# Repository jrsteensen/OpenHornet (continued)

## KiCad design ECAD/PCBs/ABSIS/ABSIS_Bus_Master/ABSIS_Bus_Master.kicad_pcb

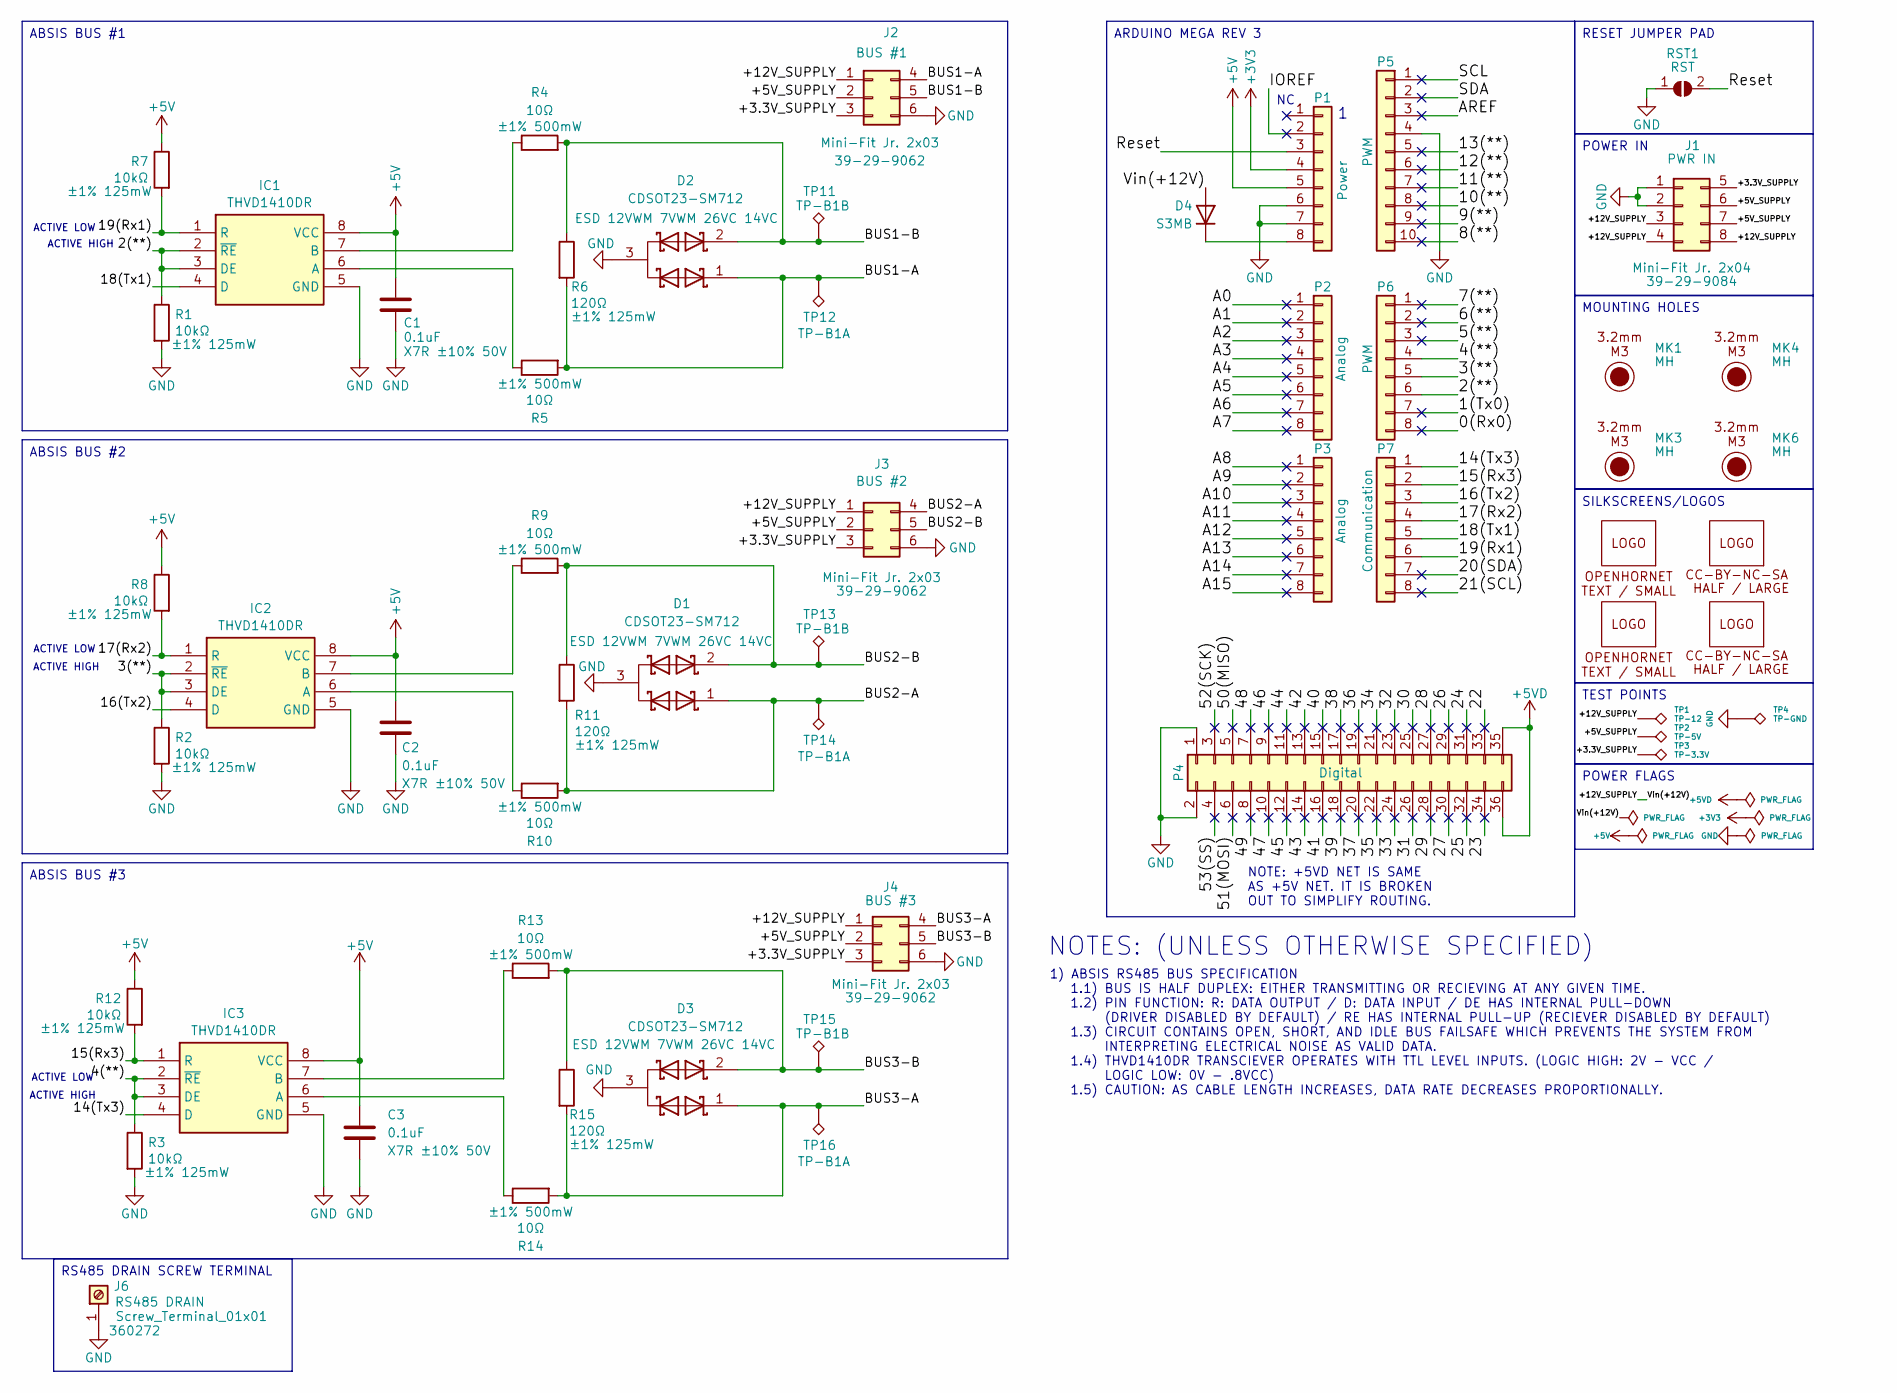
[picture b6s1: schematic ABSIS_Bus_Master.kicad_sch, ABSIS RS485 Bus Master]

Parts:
C1, C2, C3: 0.1uF; C_0805_2012Metric; Manufacturer PN CC0805KRX7R9BB104; LCSC C49678
D1, D2, D3: CDSOT23-SM712; Manufacturer PN CDSOT23-SM712; LCSC C404012
D4: S3MB; D_SMB; Manufacturer PN S3MB; LCSC C47524
IC1, IC2, IC3: THVD1410DR; Manufacturer PN THVD1410DR; LCSC C2671345
J1: Mini-Fit Jr. 2x04; Molex_Mini-Fit_Jr_5566-08A2_2x04_P4.20mm_Vertical; Manufacturer PN 39-29-9084; LCSC C587470
J2, J3, J4: Mini-Fit Jr. 2x03; Molex_Mini-Fit_Jr_5566-06A2_2x03_P4.20mm_Vertical; Manufacturer PN 39-29-9062; LCSC C505177
J6: Screw_Terminal_01x01; TerminalBlock_MetzConnect_360272_1x01_Horizontal_ScrewM2.6; Manufacturer PN 360272
LOGO1, LOGO4: LOGO; LOGO_CC-BY-NC-SA_Half_Large
LOGO2, LOGO3: LOGO; LOGO_OH_Text_Small
MK1, MK3, MK4, MK6: MH; MountingHole_3.2mm_M3_DIN965
P1: Power; PinHeader_1x08_P2.54mm_Vertical
P2, P3: Analog; PinHeader_1x08_P2.54mm_Vertical
P4: Digital; PinHeader_2x18_P2.54mm_Vertical
P5: PWM; PinHeader_1x10_P2.54mm_Vertical
P6: PWM; PinHeader_1x08_P2.54mm_Vertical
P7: Communication; PinHeader_1x08_P2.54mm_Vertical
R1, R2, R3, R7, R8, R12: 10kΩ; R_0805_2012Metric; Manufacturer PN AC0805FR-0710KL; LCSC C140868
R4, R5, R9, R10, R13, R14: 10Ω; R_0805_2012Metric; Manufacturer PN CRCW080510R0FKEAHP; LCSC C844598
R6, R11, R15: 120Ω; R_0805_2012Metric; Manufacturer PN CRCW0805120RFKEA; LCSC C844816
RST1: RST; SolderJumper-2_P1.3mm_Open_RoundedPad1.0x1.5mm
TP1: TP-12; TestPoint_THTPad_D1.5mm_Drill0.7mm
TP2: TP-5V; TestPoint_THTPad_D1.5mm_Drill0.7mm
TP3: TP-3.3V; TestPoint_THTPad_D1.5mm_Drill0.7mm
TP4: TP-GND; TestPoint_THTPad_D1.5mm_Drill0.7mm
TP11, TP13, TP15: TP-B1B; TestPoint_THTPad_D1.5mm_Drill0.7mm
TP12, TP14, TP16: TP-B1A; TestPoint_THTPad_D1.5mm_Drill0.7mm

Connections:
+3V3: P1.4
+5V: C1.2, C2.2, C3.2, IC1.8 (VCC), IC2.8 (VCC), IC3.8 (VCC), P1.5, R7.1, R8.1, R12.1
+5VD: P4.35, P4.36
/0(Rx0): P6.8
/1(Tx0): P6.7
/2(**): IC1.2 (~RE), IC1.3 (DE), P6.6, R1.1
/3(**): IC2.2 (~RE), IC2.3 (DE), P6.5, R2.1
/4(**): IC3.2 (~RE), IC3.3 (DE), P6.4, R3.1
/5(**): P6.3
/6(**): P6.2
/7(**): P6.1
/8(**): P5.10
/9(**): P5.9
/10(**): P5.8
/11(**): P5.7
/12(**): P5.6
/13(**): P5.5
/14(Tx3): IC3.4 (D), P7.1
/15(Rx3): IC3.1 (R), P7.2, R12.2
/16(Tx2): IC2.4 (D), P7.3
/17(Rx2): IC2.1 (R), P7.4, R8.2
/18(Tx1): IC1.4 (D), P7.5
/19(Rx1): IC1.1 (R), P7.6, R7.2
/20(SDA): P7.7
/21(SCL): P7.8
/22: P4.33
/23: P4.34
/24: P4.31
/25: P4.32
/26: P4.29
/27: P4.30
/28: P4.27
/29: P4.28
/30: P4.25
/31: P4.26
/32: P4.23
/33: P4.24
/34: P4.21
/35: P4.22
/36: P4.19
/37: P4.20
/38: P4.17
/39: P4.18
/40: P4.15
/41: P4.16
/42: P4.13
/43: P4.14
/44: P4.11
/45: P4.12
/46: P4.9
/47: P4.10
/48: P4.7
/49: P4.8
/50(MISO): P4.5
/51(MOSI): P4.6
/52(SCK): P4.3
/53(SS): P4.4
/+3.3V_SUPPLY: J1.5, J2.3, J3.3, J4.3, TP3.1 (1_1)
/+5V_SUPPLY: J1.6, J1.7, J2.2, J3.2, J4.2, TP2.1 (1_1)
/+12V_SUPPLY: D4.2 (A), J1.3, J1.4, J1.8, J2.1, J3.1, J4.1, TP1.1 (1_1)
/A0: P2.1
/A1: P2.2
/A2: P2.3
/A3: P2.4
/A4: P2.5
/A5: P2.6
/A6: P2.7
/A7: P2.8
/A8: P3.1
/A9: P3.2
/A10: P3.3
/A11: P3.4
/A12: P3.5
/A13: P3.6
/A14: P3.7
/A15: P3.8
/AREF: P5.3
/BUS1-A: D2.1, J2.4, R5.2, R6.2, TP12.1 (1_1)
/BUS1-B: D2.2, J2.5, R4.2, R6.1, TP11.1 (1_1)
/BUS2-A: D1.1, J3.4, R10.2, R11.2, TP14.1 (1_1)
/BUS2-B: D1.2, J3.5, R9.2, R11.1, TP13.1 (1_1)
/BUS3-A: D3.1, J4.4, R14.2, R15.2, TP16.1 (1_1)
/BUS3-B: D3.2, J4.5, R13.2, R15.1, TP15.1 (1_1)
/IOREF: P1.2
/Reset: P1.3, RST1.2 (B)
/SCL: P5.1
/SDA: P5.2
GND: C1.1, C2.1, C3.1, D1.3, D2.3, D3.3, IC1.5 (GND), IC2.5 (GND), IC3.5 (GND), J1.1, J1.2, J2.6, J3.6, J4.6, J6.1 (Pin_1_1), P1.6, P1.7, P4.1, P4.2, P5.4, R1.2, R2.2, R3.2, RST1.1 (A), TP4.1 (1_1)
unnamed: D4.1 (K), P1.8
unnamed: IC1.6 (A), R5.1
unnamed: IC1.7 (B), R4.1
unnamed: IC2.6 (A), R10.1
unnamed: IC2.7 (B), R9.1
unnamed: IC3.6 (A), R14.1
unnamed: IC3.7 (B), R13.1

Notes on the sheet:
ACTIVE HIGH
ACTIVE LOW
NOTES: (UNLESS OTHERWISE SPECIFIED)
NOTE: +5VD NET IS SAME AS +5V NET. IT IS BROKEN OUT TO SIMPLIFY ROUTING.
1) ABSIS RS485 BUS SPECIFICATION 1.1) BUS IS HALF DUPLEX: EITHER TRANSMITTING OR RECIEVING AT ANY GIVEN TIME. 1.2) PIN FUNCTION: R: DATA OUTPUT / D: DATA INPUT / DE HAS INTERNAL PULL-DOWN (DRIVER DISABLED BY DEFAULT) / RE HAS INTERNAL PULL-UP (RECIEVER DISABLED BY DEFAULT) 1.3) CIRCUIT CONTAINS OPE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
POWER IN
MOUNTING HOLES
POWER FLAGS
ABSIS BUS #1
ABSIS BUS #3
ABSIS BUS #2
RS485 DRAIN SCREW TERMINAL
ARDUINO MEGA REV 3
RESET JUMPER PAD
TEST POINTS
SILKSCREENS/LOGOS

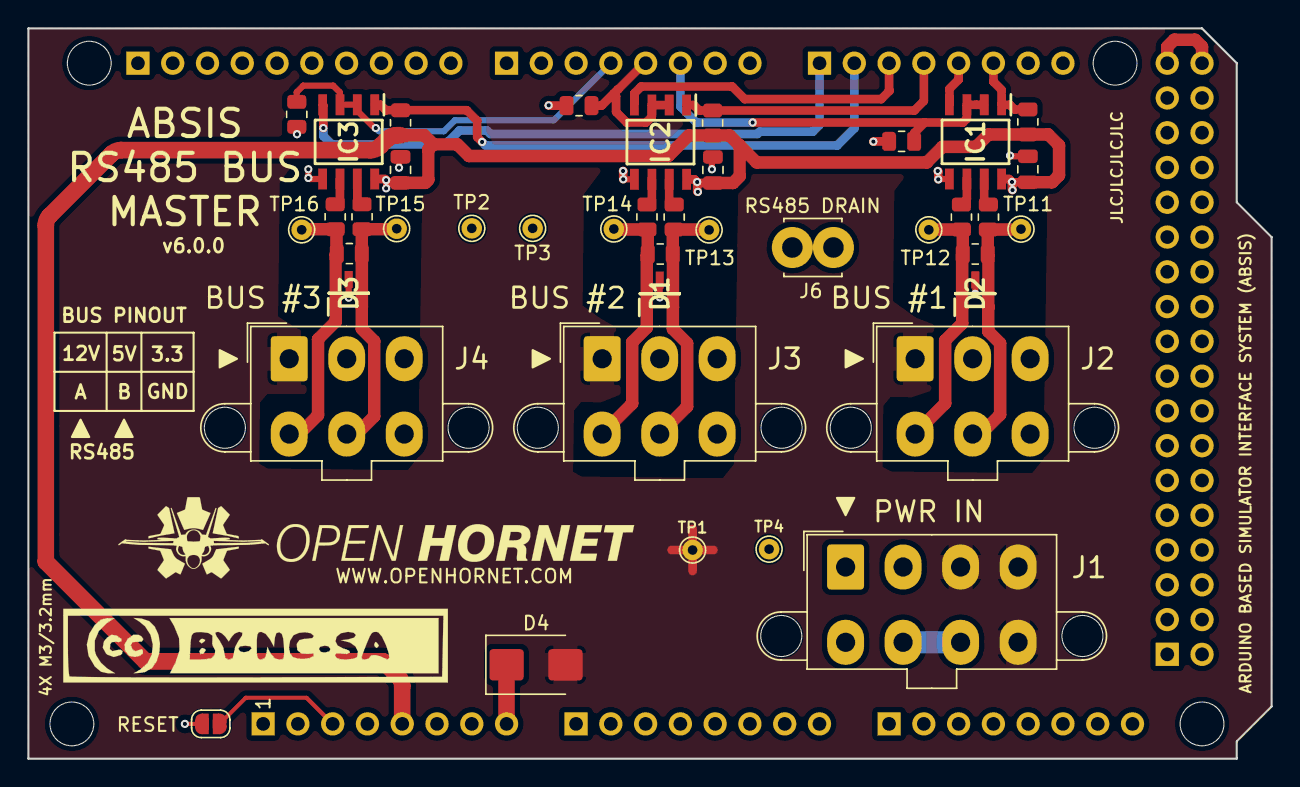
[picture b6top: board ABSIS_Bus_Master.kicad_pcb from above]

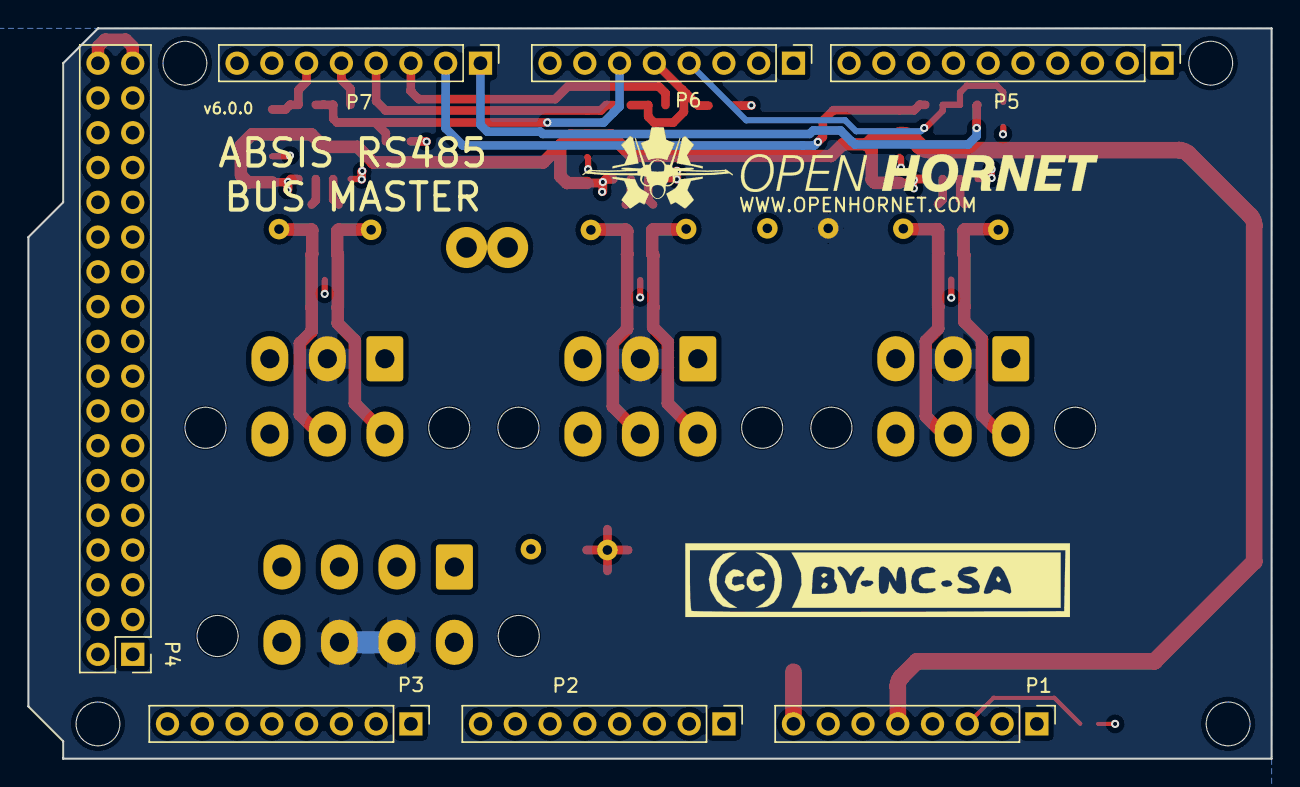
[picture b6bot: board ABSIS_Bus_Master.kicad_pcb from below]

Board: 4 copper layers, 90.8 x 53.3 mm, 56 parts (9 on the bottom side), 29 nets.

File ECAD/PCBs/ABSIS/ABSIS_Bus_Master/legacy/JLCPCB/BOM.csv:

"Reference","Value","Datasheet","Footprint","Qty","DNP","#","LCSC","Manufacturer PN","Description"
"C1,C2,C3","0.1uF","https://datasheet.lcsc.com/szlcsc/YAGEO-CChttps://datasheet.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","Capacitor_SMD:C_0805_2012Metric","3","","1","C49678","CC0805KRX7R9BB104","X7R ±10% 50V"
"D1,D2,D3","CDSOT23-SM712","https://www.lcsc.com/datasheet/C404012.pdf?spm=wm.sxq.inf.gg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","CDSOT23-SM712:CDSOT23-SM712","3","","2","C404012","CDSOT23-SM712","ESD 12VWM 7VWM 26VC 14VC"
"D4","SS54","https://datasheet.lcsc.com/szlcsc/1903042030_MDD-Jiangsu-Yut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","SS54:SS54","1","","3","C22452","SS54","SURFACE MOUNT SCHOTTKY BARRIER RECTIFIER."
"IC1,IC2,IC3","THVD1410DR","https://www.ti.com/lit/ds/symlink/thvd1410.pdf?HQS=dis-dk-nu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","THVD1410DR:THVD1410DR","3","","4","C2671345","THVD1410DR","3.3-V to 5-V RS-485 transceiver with +/-18-kV IEC ESD protection"
"J1","Mini-Fit Jr. 2x04","https://datasheet.lcsc.com/lcsc/2007161933_MOLEX-39299084_C5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","OH_Footprints:Molex_Mini-Fit_Jr_5566-08A2_2x04_P4.20mm_Vertical","1","","5","C587470","39-29-9084",""
"J2,J3,J4","Mini-Fit Jr. 2x03","https://datasheet.lcsc.com/lcsc/2005291105_MOLEX-39299062_C5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","OH_Footprints:Molex_Mini-Fit_Jr_5566-06A2_2x03_P4.20mm_Vertical","3","","6","C505177","39-29-9062",""
"J5","PinHeader_2x11","https://app.adam-tech.com/products/download/data_sheet/20206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","Connector_PinHeader_2.54mm:PinHeader_2x11_P2.54mm_Vertical","1","","7","","PH2-11-UA",""
"P1","Power","","Connector_PinHeader_2.54mm:PinHeader_1x08_P2.54mm_Vertical","1","","8","","",""
"P2,P3","Analog","","Connector_PinHeader_2.54mm:PinHeader_1x08_P2.54mm_Vertical","2","","9","","",""
"P4","Digital","","Connector_PinHeader_2.54mm:PinHeader_2x18_P2.54mm_Vertical","1","","10","","",""
"P5,P6","PWM","","Connector_PinHeader_2.54mm:PinHeader_1x08_P2.54mm_Vertical,Connector_PinHeader_2.54mm:PinHeader_1x10_P2.54mm_Vertical","2","","11","","",""
"P7","Communication","","Connector_PinHeader_2.54mm:PinHeader_1x08_P2.54mm_Vertical","1","","12","","",""
"R1,R2,R3,R7,R8,R12","10kΩ","https://www.lcsc.com/datasheet/C140868.pdf?spm=wm.sxq.inf.gg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","Resistor_SMD:R_0805_2012Metric","6","","13","C140868","AC0805FR-0710KL","±1% 125mW"
"R4,R5,R9,R10,R13,R14","10Ω","https://www.vishay.com/docs/20043/crcwhpe3.pdf","Resistor_SMD:R_0805_2012Metric","6","","14","C844598","CRCW080510R0FKEAHP","±1% 500mW"
"R6,R11,R15","120Ω","https://www.lcsc.com/datasheet/C844816.pdf?spm=wm.sxq.inf.gg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","Resistor_SMD:R_0805_2012Metric","3","","15","C844816","CRCW0805120RFKEA","±1% 125mW"
"TP1","TP-12","~","TestPoint:TestPoint_THTPad_D1.5mm_Drill0.7mm","1","","16","","",""
"TP2","TP-5V","~","TestPoint:TestPoint_THTPad_D1.5mm_Drill0.7mm","1","","17","","",""
"TP3","TP-3.3V","~","TestPoint:TestPoint_THTPad_D1.5mm_Drill0.7mm","1","","18","","",""
"TP4","TP-GND","~","TestPoint:TestPoint_THTPad_D1.5mm_Drill0.7mm","1","","19","","",""
"TP11,TP13,TP15","TP-B1B","~","TestPoint:TestPoint_THTPad_D1.5mm_Drill0.7mm","3","","20","","",""
"TP12,TP14,TP16","TP-B1A","~","TestPoint:TestPoint_THTPad_D1.5mm_Drill0.7mm","3","","21","","",""
